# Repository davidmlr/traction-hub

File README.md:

# traction-hub

ESC contrlled with stm32

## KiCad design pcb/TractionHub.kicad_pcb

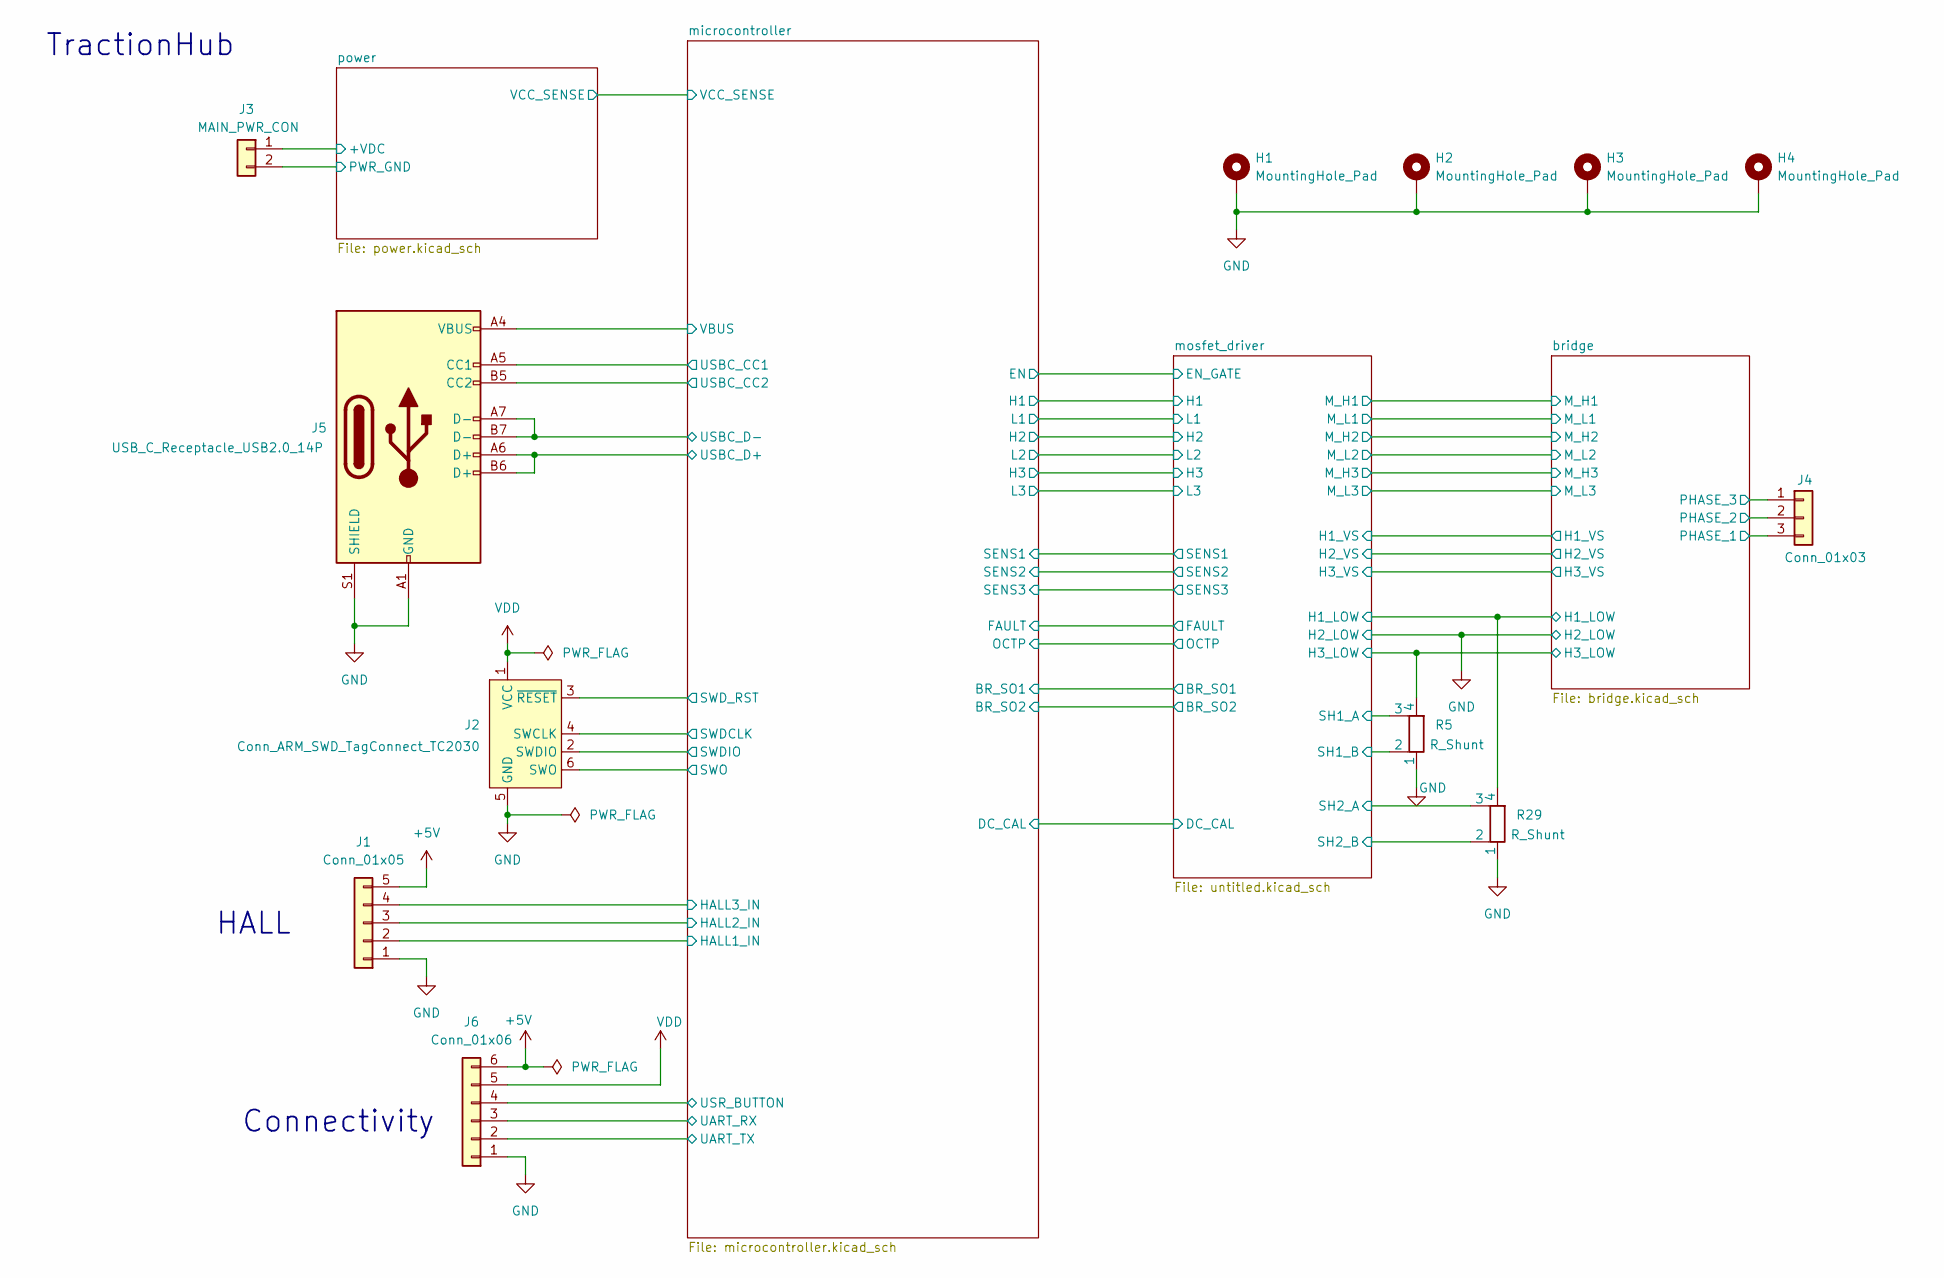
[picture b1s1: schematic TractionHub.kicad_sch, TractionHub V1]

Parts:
H1, H2, H3, H4: MountingHole_Pad; MountingHole_4.3mm_M4_Pad_Via
J1: Conn_01x05; JST_EH_B5B-EH-A_1x05_P2.50mm_Vertical
J2: Conn_ARM_SWD_TagConnect_TC2030; Tag-Connect_TC2030-IDC-FP_2x03_P1.27mm_Vertical
J3: MAIN_PWR_CON; AMASS_XT60-M_1x02_P7.20mm_Vertical
J4: Conn_01x03; cooler
J5: USB_C_Receptacle_USB2.0_14P; USB_C_Receptacle_GCT_USB4105-xx-A_16P_TopMnt_Horizontal
J6: Conn_01x06; JST_EH_B6B-EH-A_1x06_P2.50mm_Vertical
R5, R29: R_Shunt; besser

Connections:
+5V: J1.5, J6.6; also elsewhere on the board
/bridge/H1_LOW: R29.4; also elsewhere on the board
/bridge/H1_VS: J4.3; also elsewhere on the board
/bridge/H2_VS: J4.2; also elsewhere on the board
/bridge/H3_LOW: R5.4; also elsewhere on the board
/bridge/H3_VS: J4.1; also elsewhere on the board
/microcontroller/HALL1_IN: J1.2; also elsewhere on the board
/microcontroller/HALL2_IN: J1.3; also elsewhere on the board
/microcontroller/HALL3_IN: J1.4; also elsewhere on the board
/microcontroller/SWDCLK: J2.4 (SWCLK); also elsewhere on the board
/microcontroller/SWDIO: J2.2 (SWDIO); also elsewhere on the board
/microcontroller/SWD_RST: J2.3 (~RESET); also elsewhere on the board
/microcontroller/SWO: J2.6 (SWO); also elsewhere on the board
/microcontroller/UART_RX: J6.3; also elsewhere on the board
/microcontroller/UART_TX: J6.2; also elsewhere on the board
/microcontroller/USBC_CC1: J5.A5 (CC1); also elsewhere on the board
/microcontroller/USBC_CC2: J5.B5 (CC2); also elsewhere on the board
/microcontroller/USBC_D+: J5.A6 (D+), J5.B6 (D+); also elsewhere on the board
/microcontroller/USBC_D-: J5.A7 (D-), J5.B7 (D-); also elsewhere on the board
/microcontroller/USR_BUTTON: J6.4; also elsewhere on the board
/microcontroller/VBUS: J5.A4 (VBUS), J5.A9 (VBUS), J5.B4 (VBUS), J5.B9 (VBUS); also elsewhere on the board
/mosfet_driver/SH1_A: R5.3; also elsewhere on the board
/mosfet_driver/SH1_B: R5.2; also elsewhere on the board
/mosfet_driver/SH2_A: R29.3; also elsewhere on the board
/mosfet_driver/SH2_B: R29.2; also elsewhere on the board
/power/+VDC: J3.1; also elsewhere on the board
GND: H1.1, H2.1, H3.1, H4.1, J1.1, J2.5 (GND), J3.2, J5.A1 (GND), J5.A12 (GND), J5.B1 (GND), J5.B12 (GND), J5.S1 (SHIELD), J6.1, R5.1, R29.1; also elsewhere on the board
VDD: J2.1 (VCC), J6.5; also elsewhere on the board

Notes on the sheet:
HALL
TractionHub
Connectivity

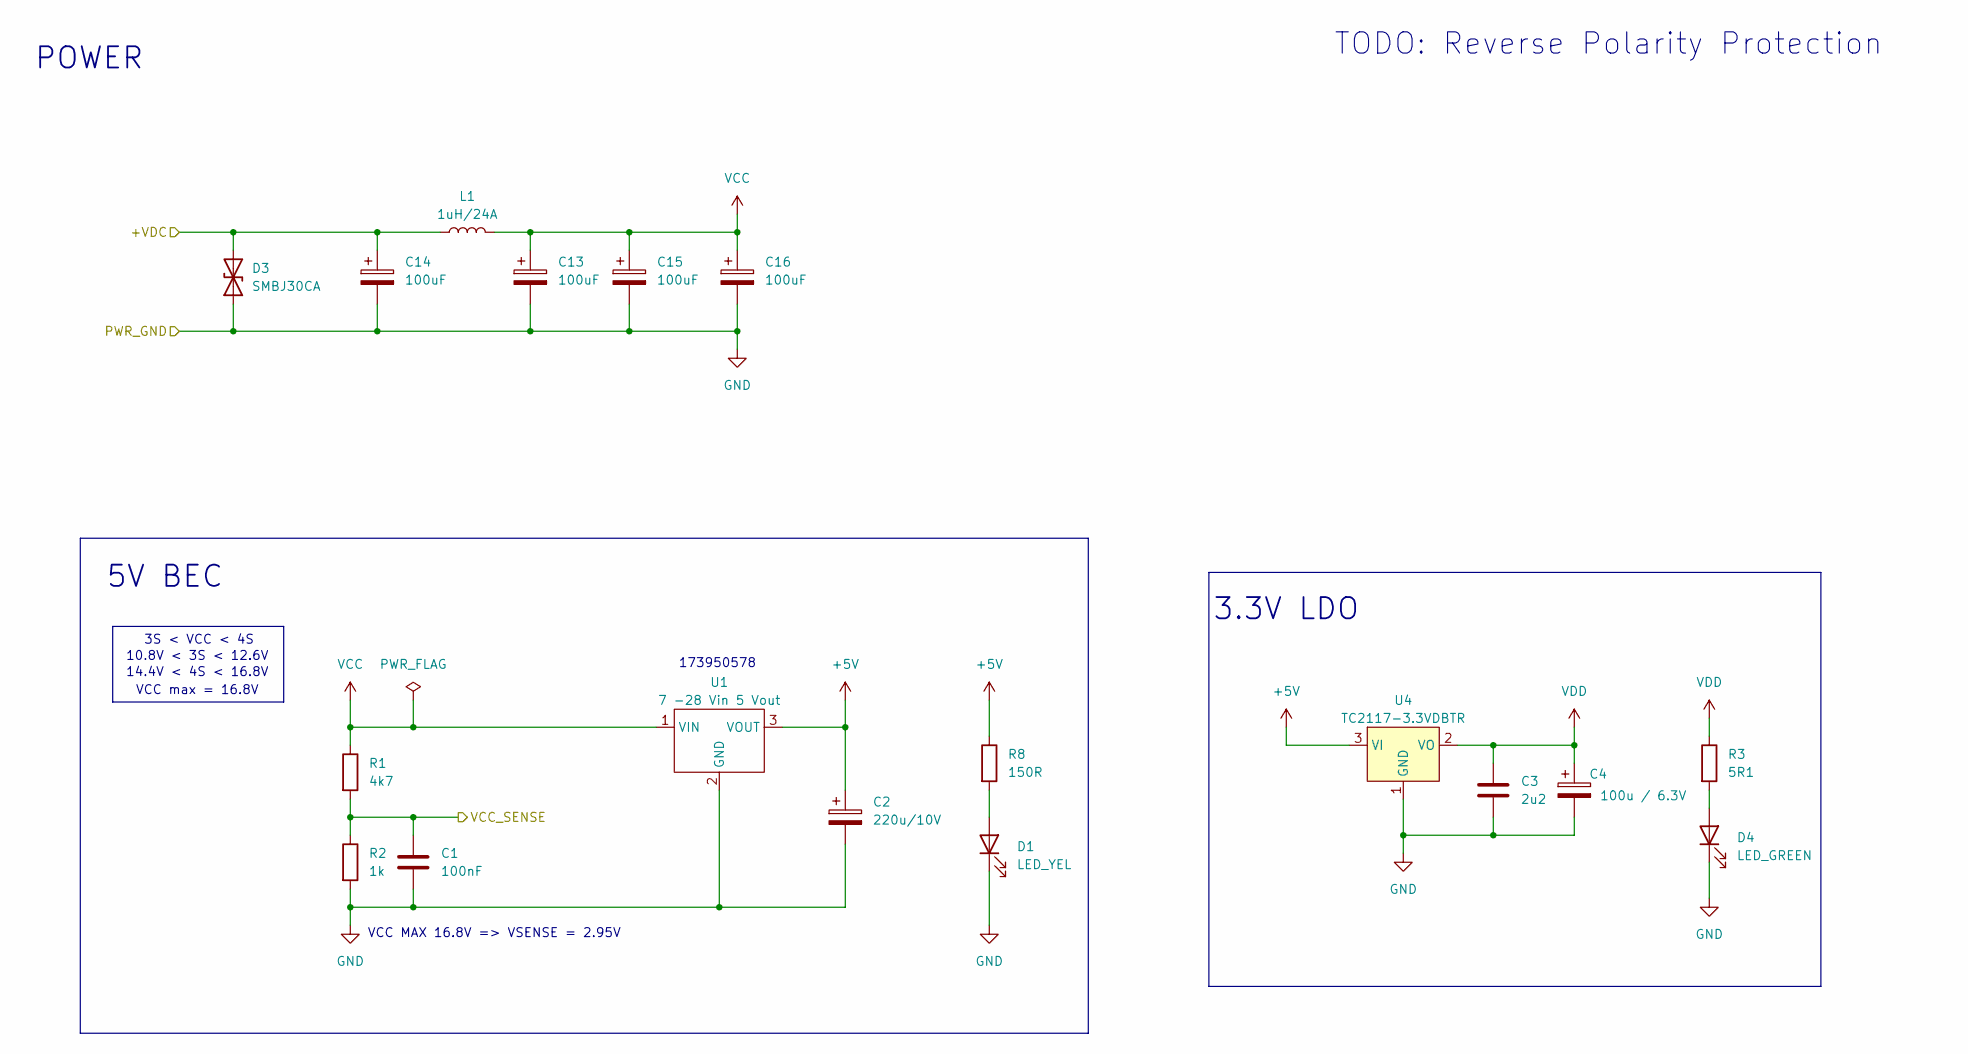
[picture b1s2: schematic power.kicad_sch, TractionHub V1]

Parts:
C1: 100nF; C_0603_1608Metric
C2: 220u/10V; 865080545012
C3: 2u2; C_0603_1608Metric
C4: 100u / 6.3V; 865080142007
C13, C14, C15, C16: 100uF; 865080545012
D1: LED_YEL; LED_0603_1608Metric
D3: SMBJ30CA; SMBJ33CA-824521331
D4: LED_GREEN; LED_0603_1608Metric
L1: 1uH/24A; 7443320100
R1: 4k7; R_0603_1608Metric
R2: 1k; R_0603_1608Metric
R3: 5R1; R_0603_1608Metric
R8: 150R; R_0603_1608Metric
U1: 7 -28 Vin 5 Vout; 173950578
U4: TC2117-3.3VDBTR; SOT-223-3_TabPin2

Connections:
+5V: C2.1, R8.1, U1.3 (VOUT), U4.3 (VI); also elsewhere on the board
/microcontroller/VCC_SENSE: C1.1, R1.2, R2.1; also elsewhere on the board
/power/+VDC: C14.1, D3.2 (A2), L1.1; also elsewhere on the board
GND: C1.2, C2.2, C3.2, C4.2, C13.2, C14.2, C15.2, C16.2, D1.1 (K), D3.1 (A1), D4.1 (K), R2.2, U1.2 (GND), U4.1 (GND); also elsewhere on the board
unnamed: D1.2 (A), R8.2
unnamed: D4.2 (A), R3.2
VCC: C13.1, C15.1, C16.1, L1.2, R1.1, U1.1 (VIN); also elsewhere on the board
VDD: C3.1, C4.1, R3.1, U4.2 (VO); also elsewhere on the board

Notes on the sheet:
5V BEC
POWER
3S < VCC < 4S
TODO: Reverse Polarity Protection
14.4V < 4S < 16.8V
10.8V < 3S < 12.6V
VCC MAX 16.8V => VSENSE = 2.95V
VCC max = 16.8V
3.3V LDO
173950578

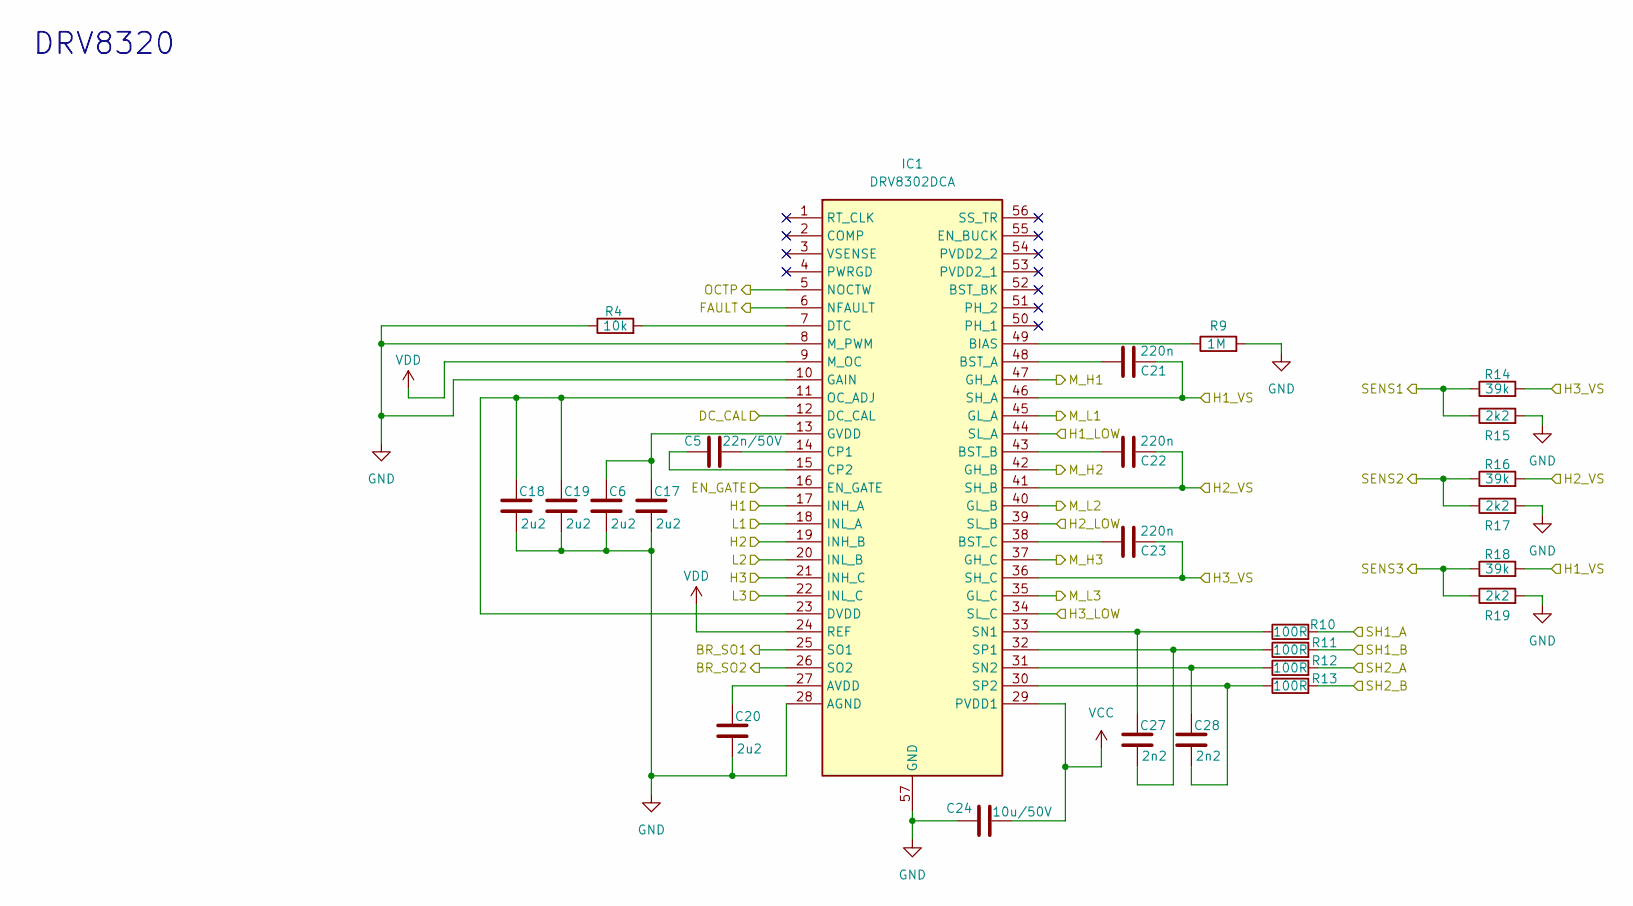
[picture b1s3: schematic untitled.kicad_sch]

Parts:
C5: 22n/50V; C_0603_1608Metric
C6, C17, C18, C19, C20: 2u2; C_0603_1608Metric
C21, C22, C23: 220n; C_0603_1608Metric
C24: 10u/50V; C_1206_3216Metric
C27, C28: 2n2; C_0603_1608Metric
IC1: DRV8302DCA; SOP50P810X120-57N; Mouser Part Number 595-DRV8302DCA
R4: 10k; C_0603_1608Metric
R9: 1M; C_0603_1608Metric
R10, R11, R12, R13: 100R; R_0603_1608Metric
R14, R16, R18: 39k; R_0603_1608Metric
R15, R17, R19: 2k2; R_0603_1608Metric

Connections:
/bridge/H1_LOW: IC1.44 (SL_A); also elsewhere on the board
/bridge/H1_VS: C21.2, IC1.46 (SH_A), R18.2; also elsewhere on the board
/bridge/H2_VS: C22.2, IC1.41 (SH_B), R16.2; also elsewhere on the board
/bridge/H3_LOW: IC1.34 (SL_C); also elsewhere on the board
/bridge/H3_VS: C23.2, IC1.36 (SH_C), R14.2; also elsewhere on the board
/bridge/M_H1: IC1.47 (GH_A); also elsewhere on the board
/bridge/M_H2: IC1.42 (GH_B); also elsewhere on the board
/bridge/M_H3: IC1.37 (GH_C); also elsewhere on the board
/bridge/M_L1: IC1.45 (GL_A); also elsewhere on the board
/bridge/M_L2: IC1.40 (GL_B); also elsewhere on the board
/bridge/M_L3: IC1.35 (GL_C); also elsewhere on the board
/microcontroller/BR_SO1: IC1.25 (SO1); also elsewhere on the board
/microcontroller/BR_SO2: IC1.26 (SO2); also elsewhere on the board
/microcontroller/DC_CAL: IC1.12 (DC_CAL); also elsewhere on the board
/microcontroller/EN: IC1.16 (EN_GATE); also elsewhere on the board
/microcontroller/FAULT: IC1.6 (NFAULT); also elsewhere on the board
/microcontroller/H1: IC1.17 (INH_A); also elsewhere on the board
/microcontroller/H2: IC1.19 (INH_B); also elsewhere on the board
/microcontroller/H3: IC1.21 (INH_C); also elsewhere on the board
/microcontroller/L1: IC1.18 (INL_A); also elsewhere on the board
/microcontroller/L2: IC1.20 (INL_B); also elsewhere on the board
/microcontroller/L3: IC1.22 (INL_C); also elsewhere on the board
/microcontroller/OCTP: IC1.5 (NOCTW); also elsewhere on the board
/microcontroller/SENS1: R14.1, R15.1; also elsewhere on the board
/microcontroller/SENS2: R16.1, R17.1; also elsewhere on the board
/microcontroller/SENS3: R18.1, R19.1; also elsewhere on the board
/mosfet_driver/SH1_A: R10.2; also elsewhere on the board
/mosfet_driver/SH1_B: R11.2; also elsewhere on the board
/mosfet_driver/SH2_A: R12.2; also elsewhere on the board
/mosfet_driver/SH2_B: R13.2; also elsewhere on the board
GND: C6.2, C17.2, C18.2, C19.2, C20.2, C24.1, IC1.8 (M_PWM), IC1.10 (GAIN), IC1.28 (AGND), IC1.39 (SL_B), IC1.57 (GND), R4.1, R9.2, R15.2, R17.2, R19.2; also elsewhere on the board
unnamed: C20.1, IC1.27 (AVDD)
unnamed: IC1.49 (BIAS), R9.1
unnamed: C21.1, IC1.48 (BST_A)
unnamed: C22.1, IC1.43 (BST_B)
unnamed: C23.1, IC1.38 (BST_C)
unnamed: C5.2, IC1.14 (CP1)
unnamed: C5.1, IC1.15 (CP2)
unnamed: IC1.7 (DTC), R4.2
unnamed: C18.1, C19.1, IC1.11 (OC_ADJ), IC1.23 (DVDD)
unnamed: C6.1, C17.1, IC1.13 (GVDD)
unnamed: C27.1, IC1.33 (SN1), R10.1
unnamed: C28.1, IC1.31 (SN2), R12.1
unnamed: C27.2, IC1.32 (SP1), R11.1
unnamed: C28.2, IC1.30 (SP2), R13.1
VCC: C24.2, IC1.29 (PVDD1); also elsewhere on the board
VDD: IC1.9 (M_OC), IC1.24 (REF); also elsewhere on the board

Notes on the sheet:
DRV8320

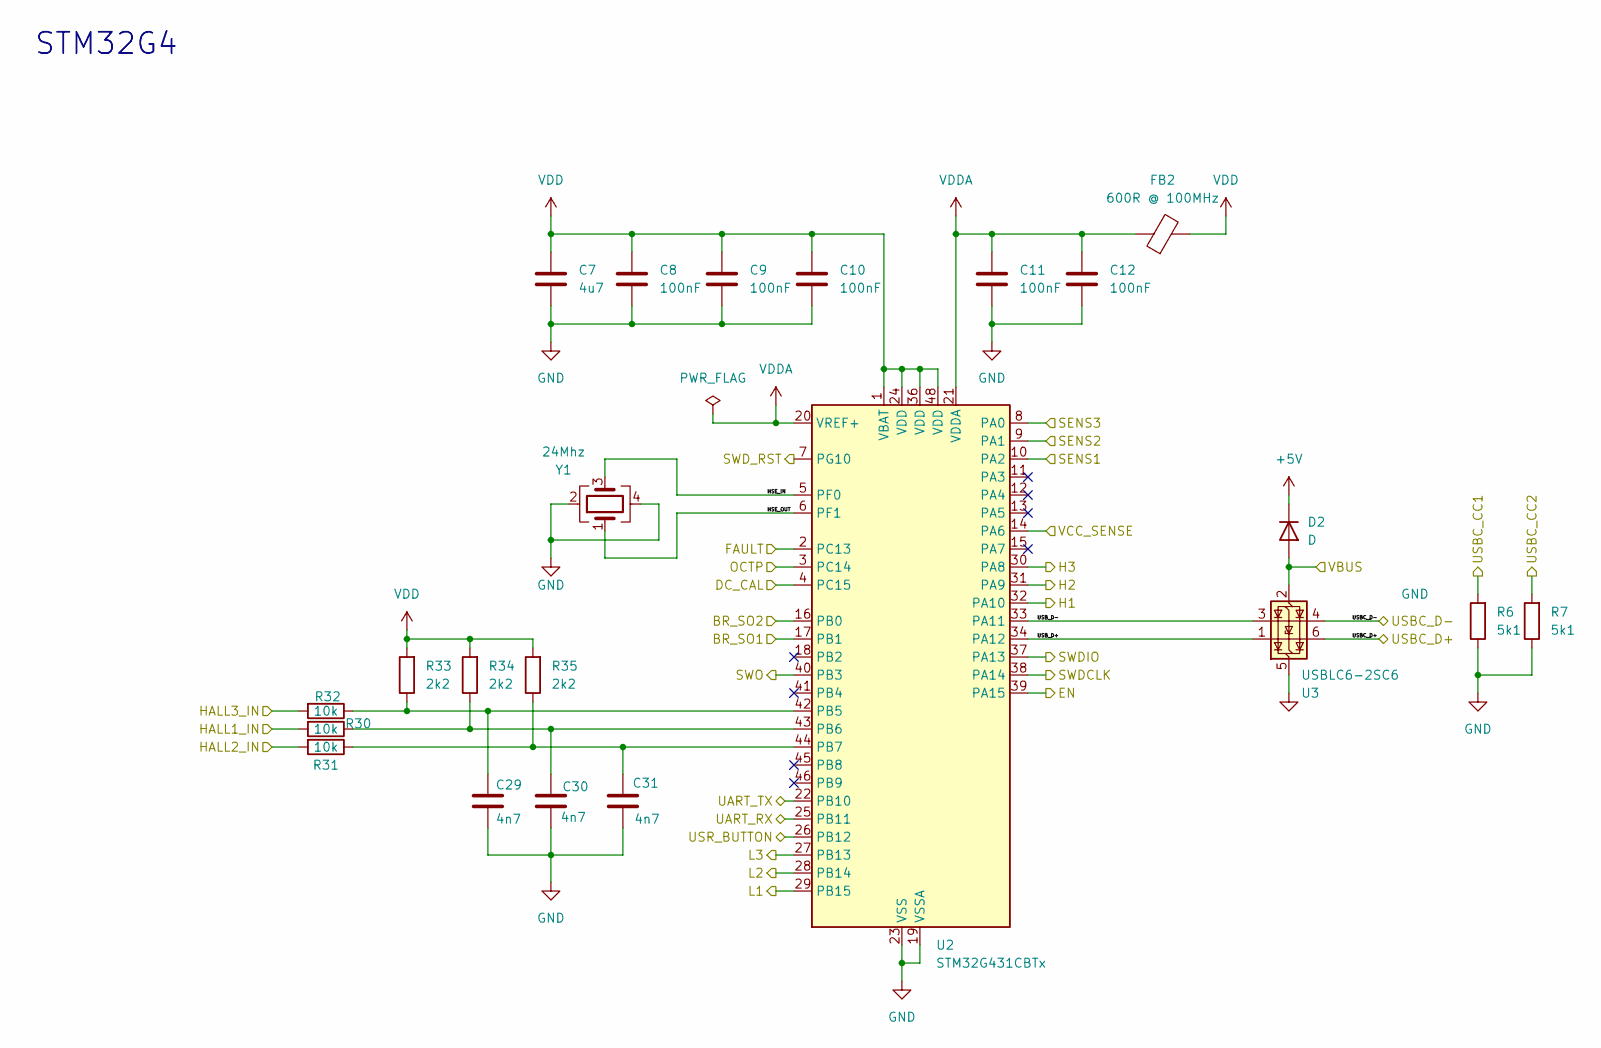
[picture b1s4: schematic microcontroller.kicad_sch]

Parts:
C7: 4u7; C_0603_1608Metric
C8, C9, C10, C11, C12: 100nF; C_0603_1608Metric
C29, C30, C31: 4n7; C_0603_1608Metric
D2: D; D_MiniMELF
FB2: 600R @ 100MHz; R_0603_1608Metric
R6, R7: 5k1; R_0603_1608Metric
R30, R31, R32: 10k; R_0603_1608Metric
R33, R34, R35: 2k2; R_0603_1608Metric
U2: STM32G431CBTx; LQFP-48_7x7mm_P0.5mm
U3: USBLC6-2SC6; SOT-23-6
Y1: 24Mhz; better_crystal

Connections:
+5V: D2.1 (K); also elsewhere on the board
/microcontroller/BR_SO1: U2.17 (PB1); also elsewhere on the board
/microcontroller/BR_SO2: U2.16 (PB0); also elsewhere on the board
/microcontroller/DC_CAL: U2.4 (PC15); also elsewhere on the board
/microcontroller/EN: U2.39 (PA15); also elsewhere on the board
/microcontroller/FAULT: U2.2 (PC13); also elsewhere on the board
/microcontroller/H1: U2.32 (PA10); also elsewhere on the board
/microcontroller/H2: U2.31 (PA9); also elsewhere on the board
/microcontroller/H3: U2.30 (PA8); also elsewhere on the board
/microcontroller/HALL1_IN: R30.2; also elsewhere on the board
/microcontroller/HALL2_IN: R31.2; also elsewhere on the board
/microcontroller/HALL3_IN: R32.2; also elsewhere on the board
/microcontroller/HSE_IN: U2.5 (PF0), Y1.3
/microcontroller/HSE_OUT: U2.6 (PF1), Y1.1
/microcontroller/L1: U2.29 (PB15); also elsewhere on the board
/microcontroller/L2: U2.28 (PB14); also elsewhere on the board
/microcontroller/L3: U2.27 (PB13); also elsewhere on the board
/microcontroller/OCTP: U2.3 (PC14); also elsewhere on the board
/microcontroller/SENS1: U2.10 (PA2); also elsewhere on the board
/microcontroller/SENS2: U2.9 (PA1); also elsewhere on the board
/microcontroller/SENS3: U2.8 (PA0); also elsewhere on the board
/microcontroller/SWDCLK: U2.38 (PA14); also elsewhere on the board
/microcontroller/SWDIO: U2.37 (PA13); also elsewhere on the board
/microcontroller/SWD_RST: U2.7 (PG10); also elsewhere on the board
/microcontroller/SWO: U2.40 (PB3); also elsewhere on the board
/microcontroller/UART_RX: U2.25 (PB11); also elsewhere on the board
/microcontroller/UART_TX: U2.22 (PB10); also elsewhere on the board
/microcontroller/USBC_CC1: R6.2; also elsewhere on the board
/microcontroller/USBC_CC2: R7.2; also elsewhere on the board
/microcontroller/USBC_D+: U3.6 (I/O1); also elsewhere on the board
/microcontroller/USBC_D-: U3.4 (I/O2); also elsewhere on the board
/microcontroller/USB_D+: U2.34 (PA12), U3.1 (I/O1)
/microcontroller/USB_D-: U2.33 (PA11), U3.3 (I/O2)
/microcontroller/USR_BUTTON: U2.26 (PB12); also elsewhere on the board
/microcontroller/VBUS: D2.2 (A), U3.2 (GND); also elsewhere on the board
/microcontroller/VCC_SENSE: U2.14 (PA6); also elsewhere on the board
GND: C7.2, C8.2, C9.2, C10.2, C11.2, C12.2, C29.2, C30.2, C31.2, R6.1, R7.1, U2.19 (VSSA), U2.23 (VSS), U2.35 (VSS), U2.47 (VSS), U3.5 (VBUS), Y1.2, Y1.4; also elsewhere on the board
unnamed: C29.1, R32.1, R33.1, U2.42 (PB5)
unnamed: C30.1, R30.1, R34.1, U2.43 (PB6)
unnamed: C31.1, R31.1, R35.1, U2.44 (PB7)
VDD: C7.1, C8.1, C9.1, C10.1, FB2.2, R33.2, R34.2, R35.2, U2.1 (VBAT), U2.24 (VDD), U2.36 (VDD), U2.48 (VDD); also elsewhere on the board
VDDA: C11.1, C12.1, FB2.1, U2.20 (VREF+), U2.21 (VDDA)

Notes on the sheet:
STM32G4

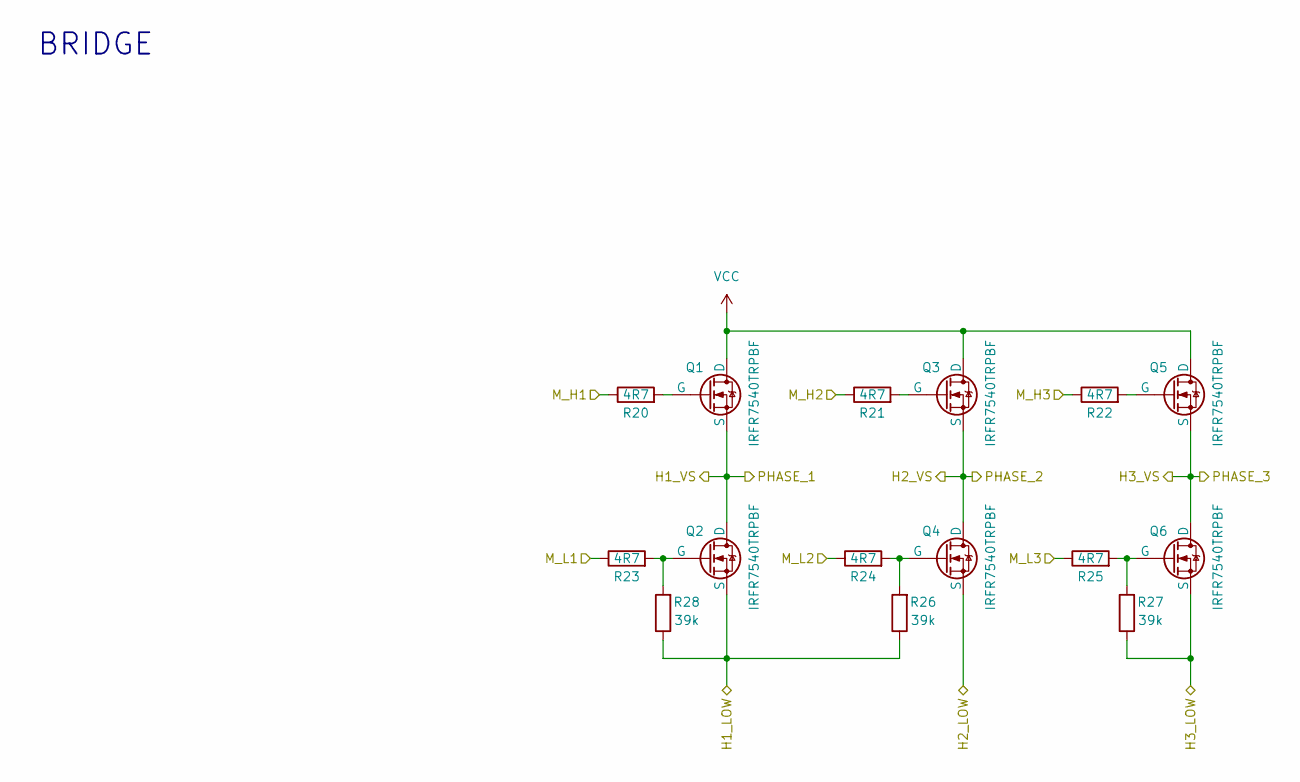
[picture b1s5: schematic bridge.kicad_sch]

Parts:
Q1, Q2, Q3, Q4, Q5, Q6: IRFR7540TRPBF; TO-252-2
R20, R21, R22, R23, R24, R25: 4R7; R_0603_1608Metric
R26, R27, R28: 39k; R_0603_1608Metric

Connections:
/bridge/H1_LOW: Q2.3 (S), R26.1, R28.1; also elsewhere on the board
/bridge/H1_VS: Q1.3 (S), Q2.2 (D); also elsewhere on the board
/bridge/H2_VS: Q3.3 (S), Q4.2 (D); also elsewhere on the board
/bridge/H3_LOW: Q6.3 (S), R27.1; also elsewhere on the board
/bridge/H3_VS: Q5.3 (S), Q6.2 (D); also elsewhere on the board
/bridge/M_H1: R20.1; also elsewhere on the board
/bridge/M_H2: R21.1; also elsewhere on the board
/bridge/M_H3: R22.1; also elsewhere on the board
/bridge/M_L1: R23.1; also elsewhere on the board
/bridge/M_L2: R24.1; also elsewhere on the board
/bridge/M_L3: R25.1; also elsewhere on the board
GND: Q4.3 (S); also elsewhere on the board
unnamed: Q1.1 (G), R20.2
unnamed: Q2.1 (G), R23.2, R28.2
unnamed: Q3.1 (G), R21.2
unnamed: Q4.1 (G), R24.2, R26.2
unnamed: Q5.1 (G), R22.2
unnamed: Q6.1 (G), R25.2, R27.2
VCC: Q1.2 (D), Q3.2 (D), Q5.2 (D); also elsewhere on the board

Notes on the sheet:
BRIDGE

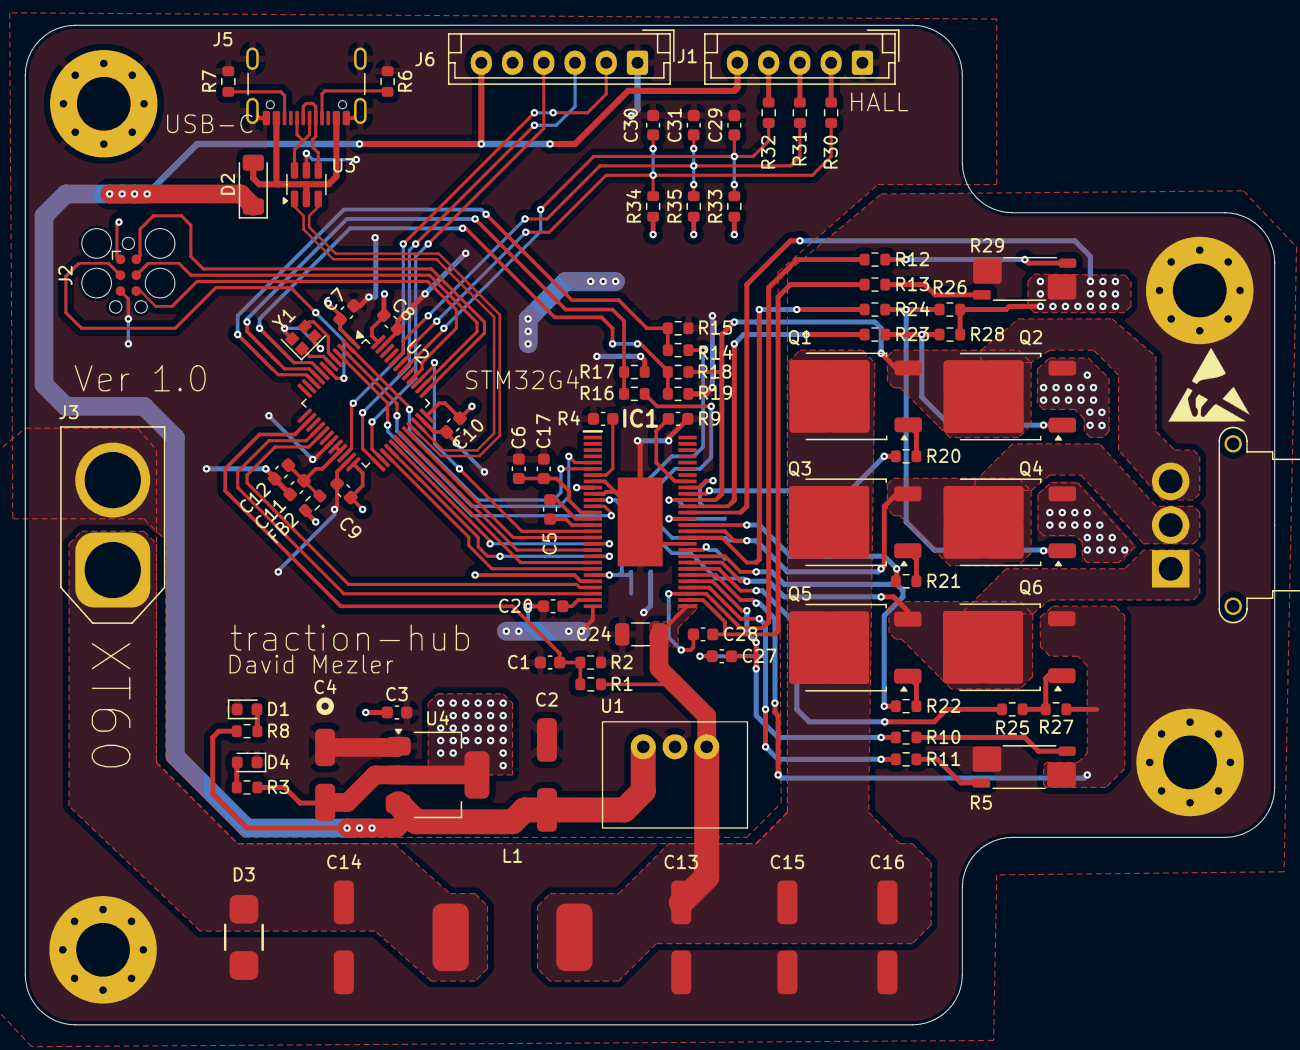
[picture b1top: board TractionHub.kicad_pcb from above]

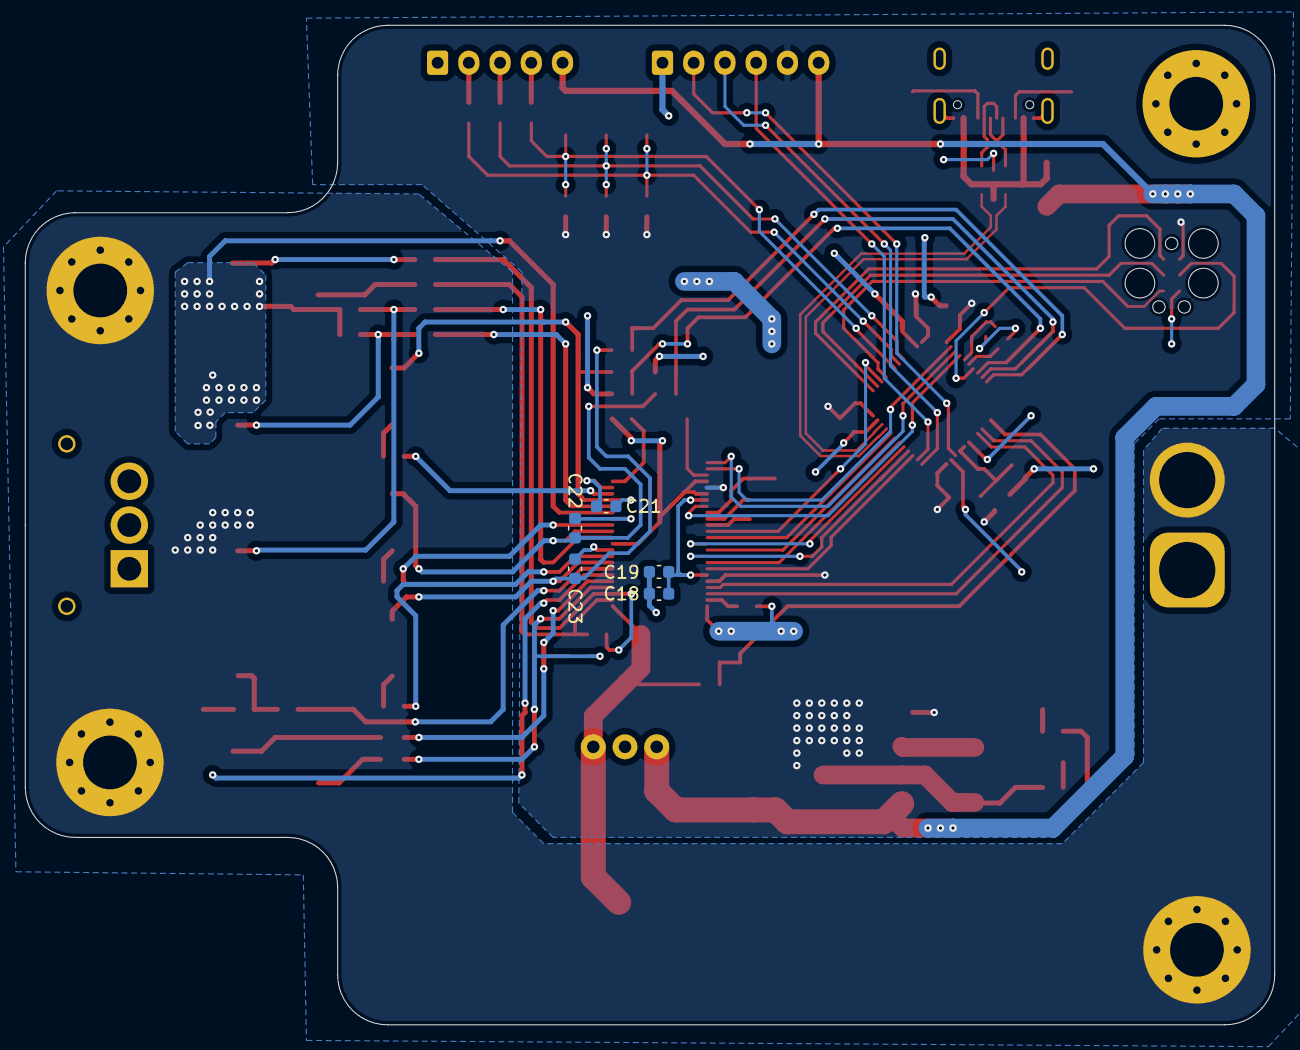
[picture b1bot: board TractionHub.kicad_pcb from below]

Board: 2 copper layers, 100.0 x 80.0 mm, 92 parts (5 on the bottom side), 81 nets.

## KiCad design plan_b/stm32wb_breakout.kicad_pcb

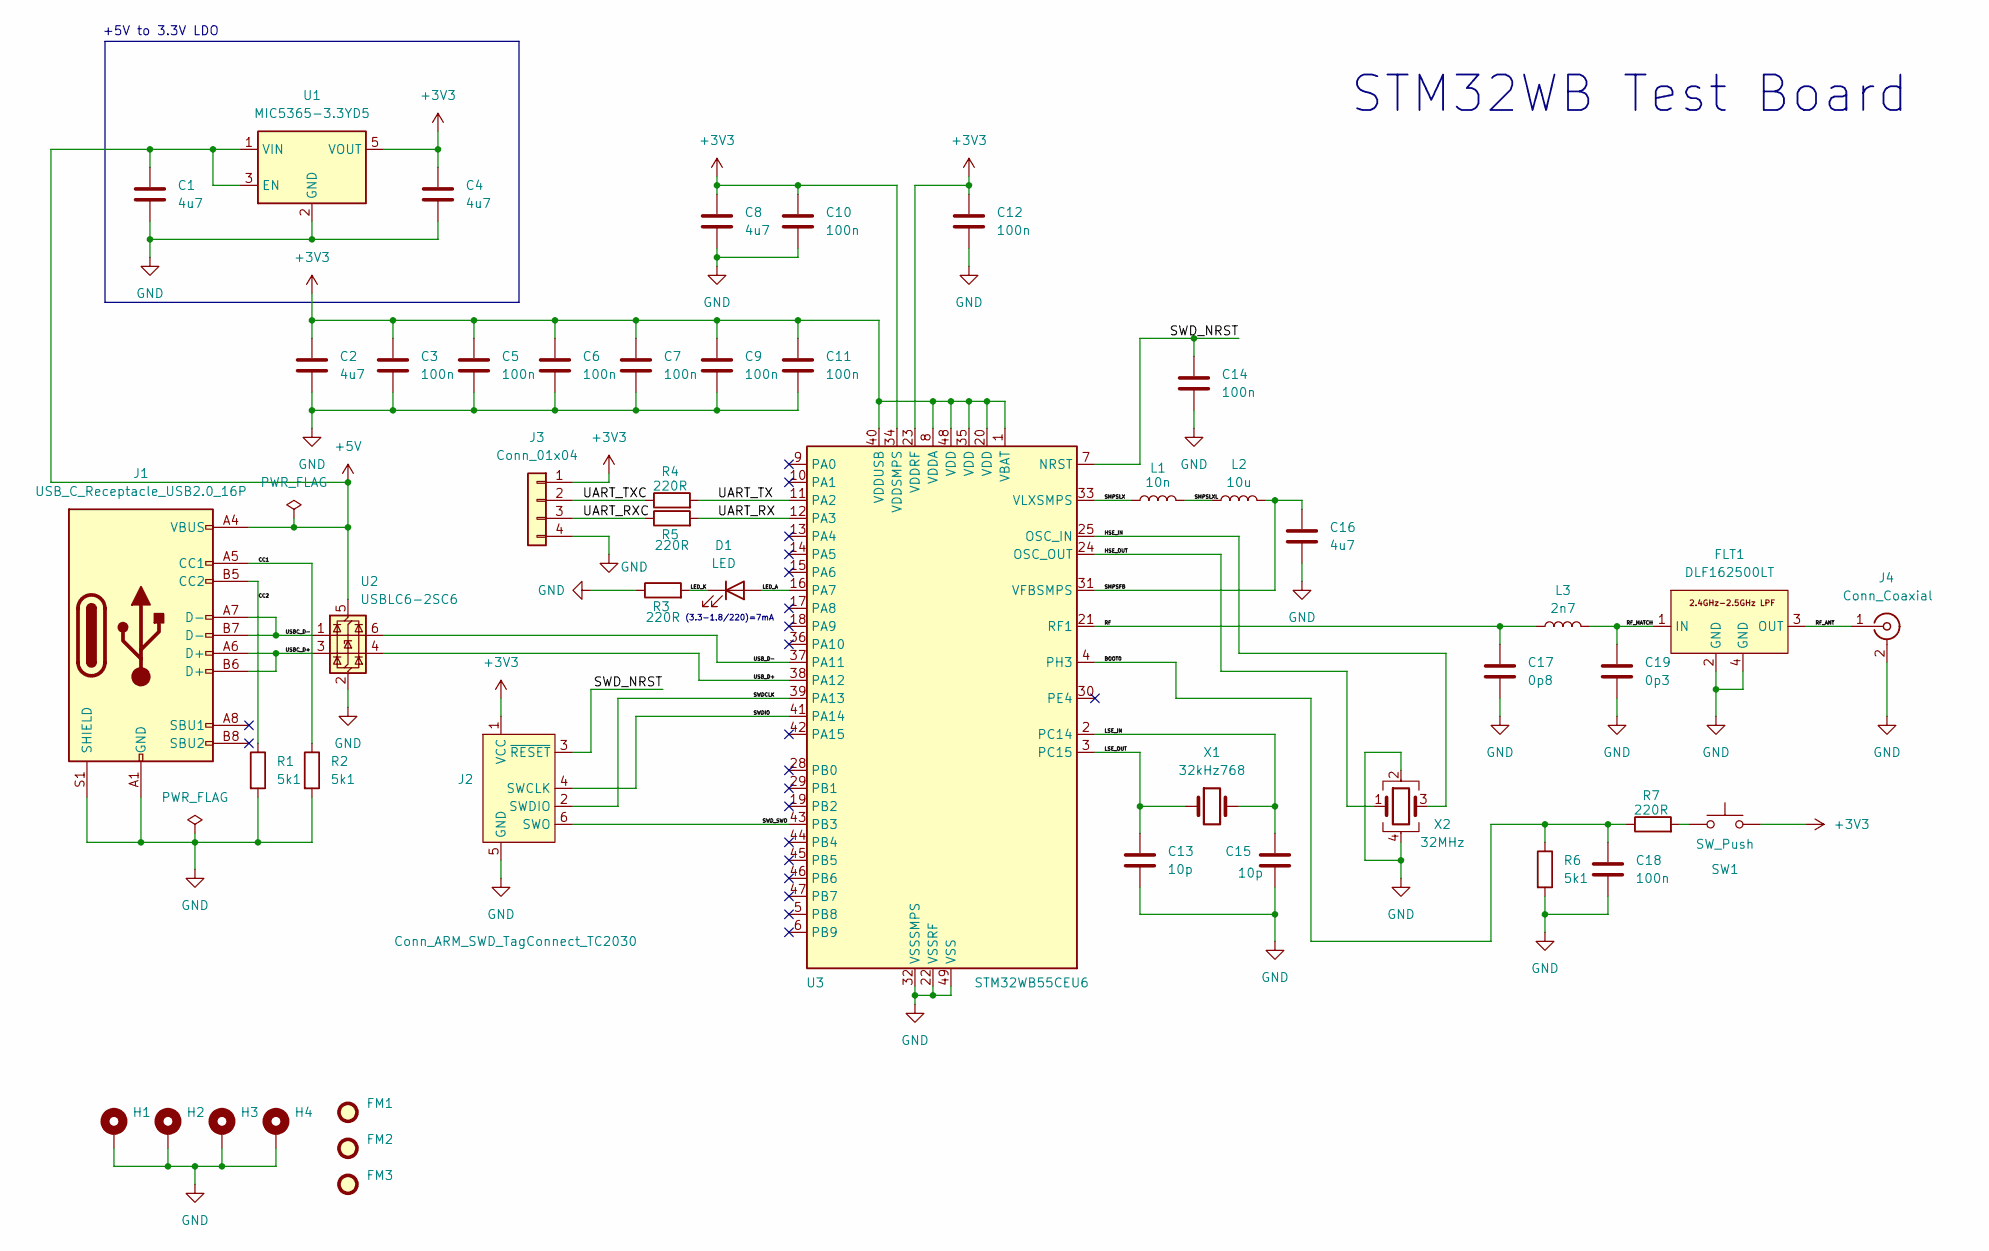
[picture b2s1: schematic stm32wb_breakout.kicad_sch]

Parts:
C1, C2, C4, C8, C16: 4u7; C_0603_1608Metric
C3, C5, C6, C7, C9, C10, C11, C12, C14, C18: 100n; C_0402_1005Metric
C13, C15: 10p; C_0402_1005Metric
C17: 0p8; C_0402_1005Metric
C19: 0p3; C_0402_1005Metric
D1: LED; LED_0402_1005Metric
FLT1: DLF162500LT
FM1, FM2, FM3: Fiducial; Fiducial_1mm_Mask2mm
H1, H2, H3, H4: MountingHole_Pad; MountingHole_2.2mm_M2_Pad_Via
J1: USB_C_Receptacle_USB2.0_16P; USB_C_Receptacle_GCT_USB4105-xx-A_16P_TopMnt_Horizontal
J2: Conn_ARM_SWD_TagConnect_TC2030; Tag-Connect_TC2030-IDC-FP_2x03_P1.27mm_Vertical
J3: Conn_01x04; Molex_PicoBlade_53048-0410_1x04_P1.25mm_Horizontal
J4: Conn_Coaxial; U.FL_Hirose_U.FL-R-SMT-1_Vertical
L1: 10n; L_0402_1005Metric
L2: 10u; L_0805_2012Metric
L3: 2n7; L_0402_1005Metric
R1, R2, R6: 5k1; R_0402_1005Metric
R3, R4, R5, R7: 220R; R_0402_1005Metric
SW1: SW_Push; SW_SPST_CK_KXT3
U1: MIC5365-3.3YD5; SOT-23-5
U2: USBLC6-2SC6; SOT-23-6
U3: STM32WB55CEU6; QFN-48-1EP_7x7mm_P0.5mm_EP5.6x5.6mm
X1: 32kHz768; Crystal_SMD_2012-2Pin_2.0x1.2mm
X2: 32MHz; Crystal_SMD_2016-4Pin_2.0x1.6mm

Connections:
+3V3: C2.1, C3.1, C4.1, C5.1, C6.1, C7.1, C8.1, C9.1, C10.1, C11.1, C12.1, J2.1 (VCC), J3.1, SW1.2, U1.5 (VOUT), U3.1 (VBAT), U3.8 (VDDA), U3.20 (VDD), U3.23 (VDDRF), U3.34 (VDDSMPS), U3.35 (VDD), U3.40 (VDDUSB), U3.48 (VDD)
+5V: C1.1, J1.A4 (VBUS), J1.A9 (VBUS), J1.B4 (VBUS), J1.B9 (VBUS), U1.1 (VIN), U1.3 (EN), U2.5 (VBUS)
/BOOT0: C18.1, R6.1, R7.1, U3.4 (PH3)
/CC1: J1.A5 (CC1), R2.1
/CC2: J1.B5 (CC2), R1.1
/HSE_IN: U3.25 (OSC_IN), X2.3
/HSE_OUT: U3.24 (OSC_OUT), X2.1
/LED_A: D1.2 (A), U3.16 (PA7)
/LED_K: D1.1 (K), R3.2
/LSE_IN: C15.1, U3.2 (PC14), X1.2
/LSE_OUT: C13.1, U3.3 (PC15), X1.1
/RF: C17.1, L3.1, U3.21 (RF1)
/RF_ANT: FLT1.3 (OUT), J4.1 (In)
/RF_MATCH: C19.1, FLT1.1 (IN), L3.2
/SMPSFB: C16.1, L2.2, U3.31 (VFBSMPS)
/SMPSLX: L1.1, U3.33 (VLXSMPS)
/SMPSLXL: L1.2, L2.1
/SWDCLK: J2.2 (SWDIO), U3.39 (PA13)
/SWDIO: J2.4 (SWCLK), U3.41 (PA14)
/SWD_NRST: C14.1, J2.3 (~RESET), U3.7 (NRST)
/SWD_SWO: J2.6 (SWO), U3.43 (PB3)
/UART_RX: R5.2, U3.12 (PA3)
/UART_RXC: J3.3, R5.1
/UART_TX: R4.2, U3.11 (PA2)
/UART_TXC: J3.2, R4.1
/USBC_D+: J1.A6 (D+), J1.B6 (D+), U2.3 (I/O2)
/USBC_D-: J1.A7 (D-), J1.B7 (D-), U2.1 (I/O1)
/USB_D+: U2.4 (I/O2), U3.38 (PA12)
/USB_D-: U2.6 (I/O1), U3.37 (PA11)
GND: C1.2, C2.2, C3.2, C4.2, C5.2, C6.2, C7.2, C8.2, C9.2, C10.2, C11.2, C12.2, C13.2, C14.2, C15.2, C16.2, C17.2, C18.2, C19.2, FLT1.2 (GND), FLT1.4 (GND), H1.1, H2.1, H3.1, H4.1, J1.A1 (GND), J1.A12 (GND), J1.B1 (GND), J1.B12 (GND), J1.S1 (SHIELD), J2.5 (GND), J3.4, J4.2 (Ext), R1.2, R2.2, R3.1, R6.2, U1.2 (GND), U2.2 (GND), U3.22 (VSSRF), U3.32 (VSSSMPS), U3.49 (VSS), X2.2, X2.4
unnamed: R7.2, SW1.1

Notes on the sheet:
STM32WB Test Board
+5V to 3.3V LDO
(3.3-1.8/220)=7mA
